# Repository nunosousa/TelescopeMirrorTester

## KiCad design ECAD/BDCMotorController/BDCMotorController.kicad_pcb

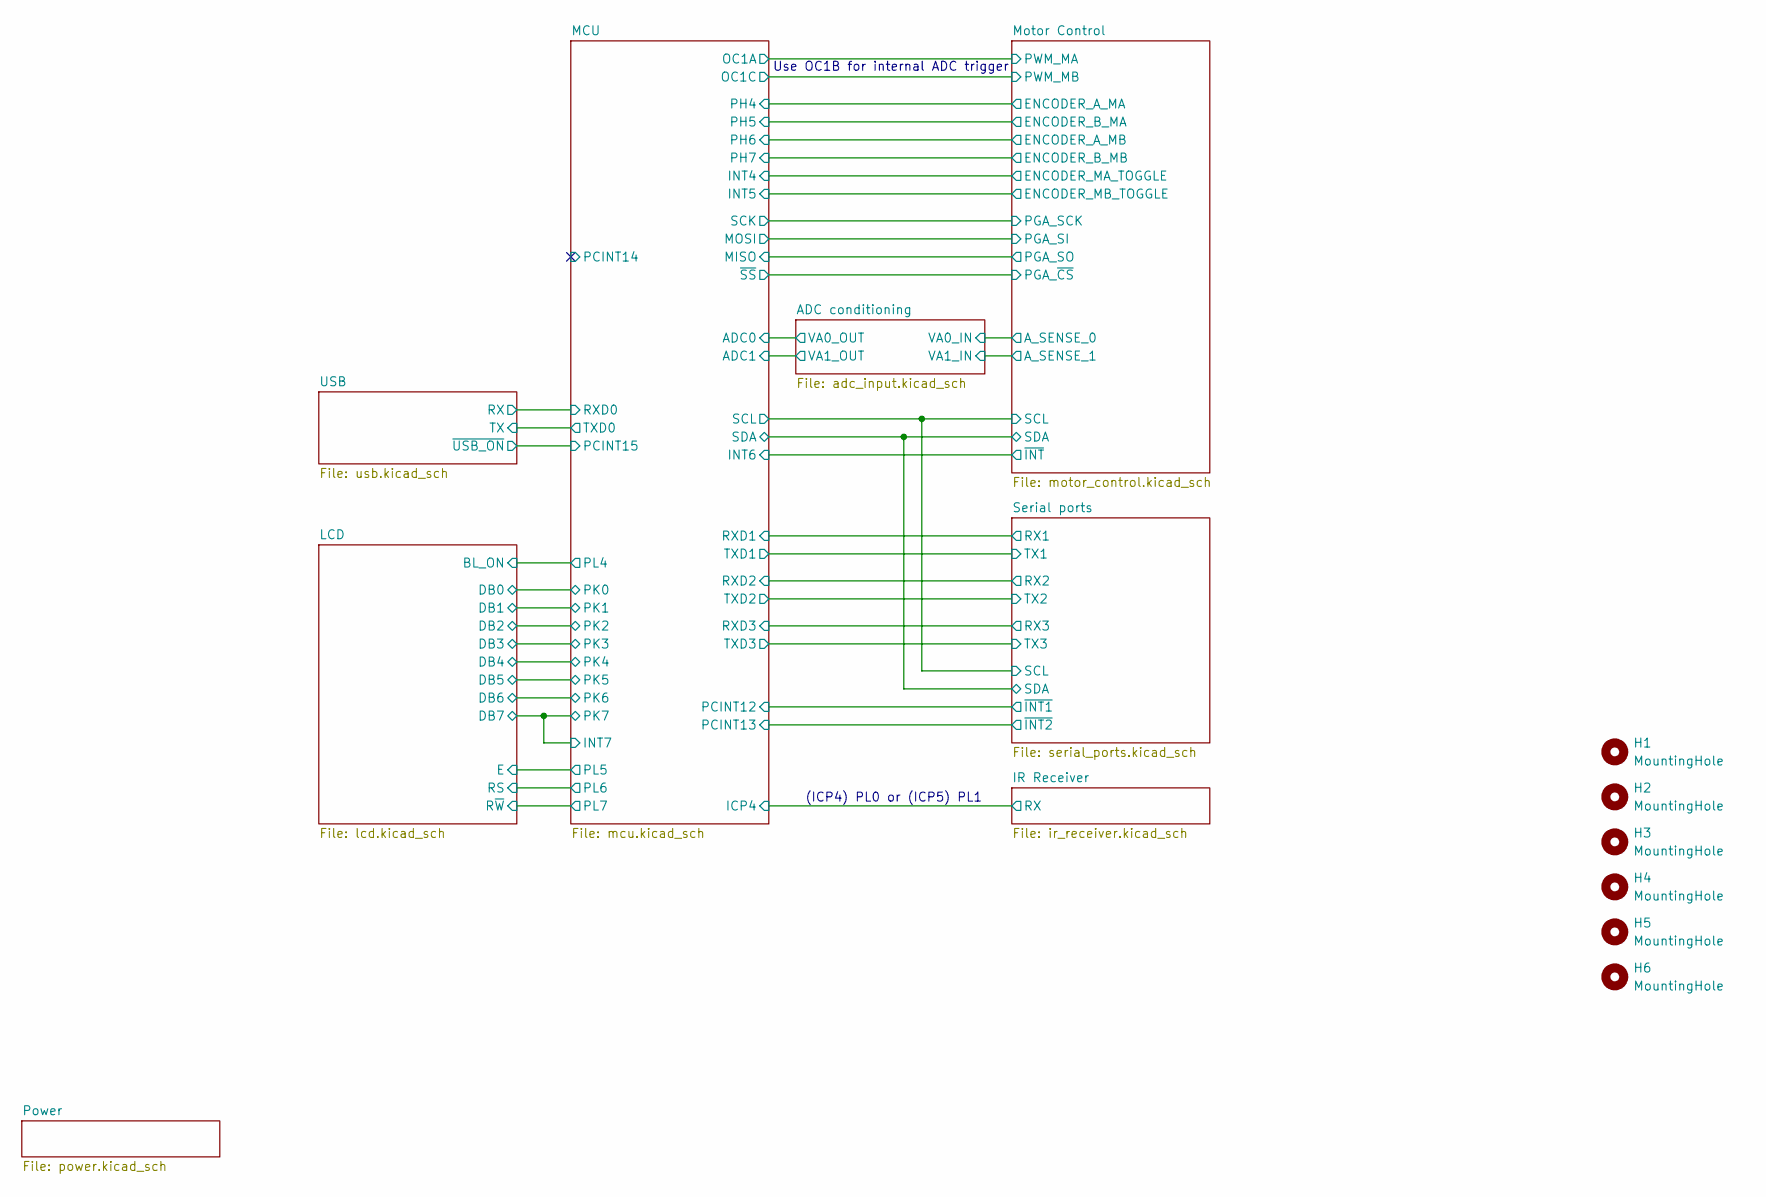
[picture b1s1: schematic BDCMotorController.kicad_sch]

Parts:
H1, H2, H3, H4, H5, H6: MountingHole; MountingHole_3.2mm_M3

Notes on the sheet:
Use OC1B for internal ADC trigger
(ICP4) PL0 or (ICP5) PL1

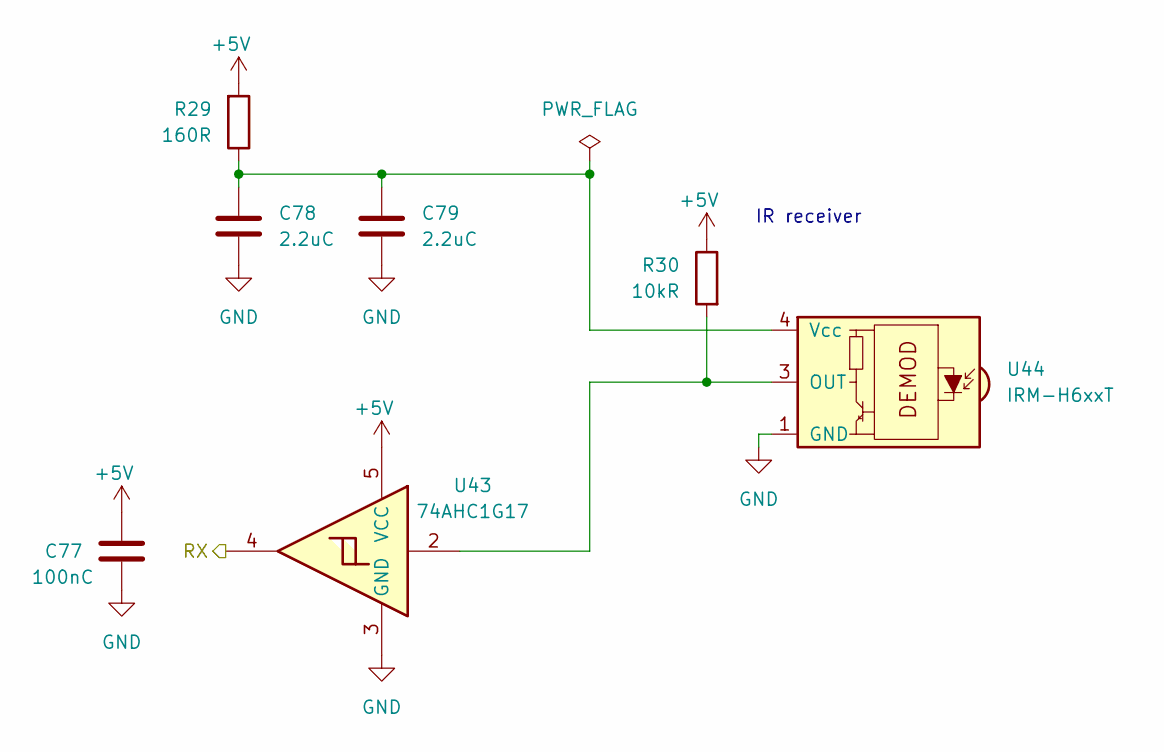
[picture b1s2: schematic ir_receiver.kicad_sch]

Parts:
C77: 100nC; C_0805_2012Metric
C78, C79: 2.2uC; C_0805_2012Metric
R29: 160R; R_0805_2012Metric; MPN AC0805FR-7W160RL
R30: 10kR; R_0805_2012Metric
U43: 74AHC1G17; SC-74A-5_1.55x2.9mm_P0.95mm; MPN 74AHC1G17GVH
U44: IRM-H6xxT; Everlight_IRM-H6xxT; MPN IRM-H638J7/TR2(CLW)

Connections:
+5V: C77.1, R29.2, R30.1, U43.5 (VCC); also elsewhere on the board
/IR Receiver/RX: U43.4; also elsewhere on the board
GND: C77.2, C78.2, C79.2, U43.3 (GND), U44.1 (GND), U44.2 (GND); also elsewhere on the board
unnamed: R30.2, U43.2, U44.3 (OUT)
unnamed: C78.1, C79.1, R29.1, U44.4 (Vcc)

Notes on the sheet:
IR receiver

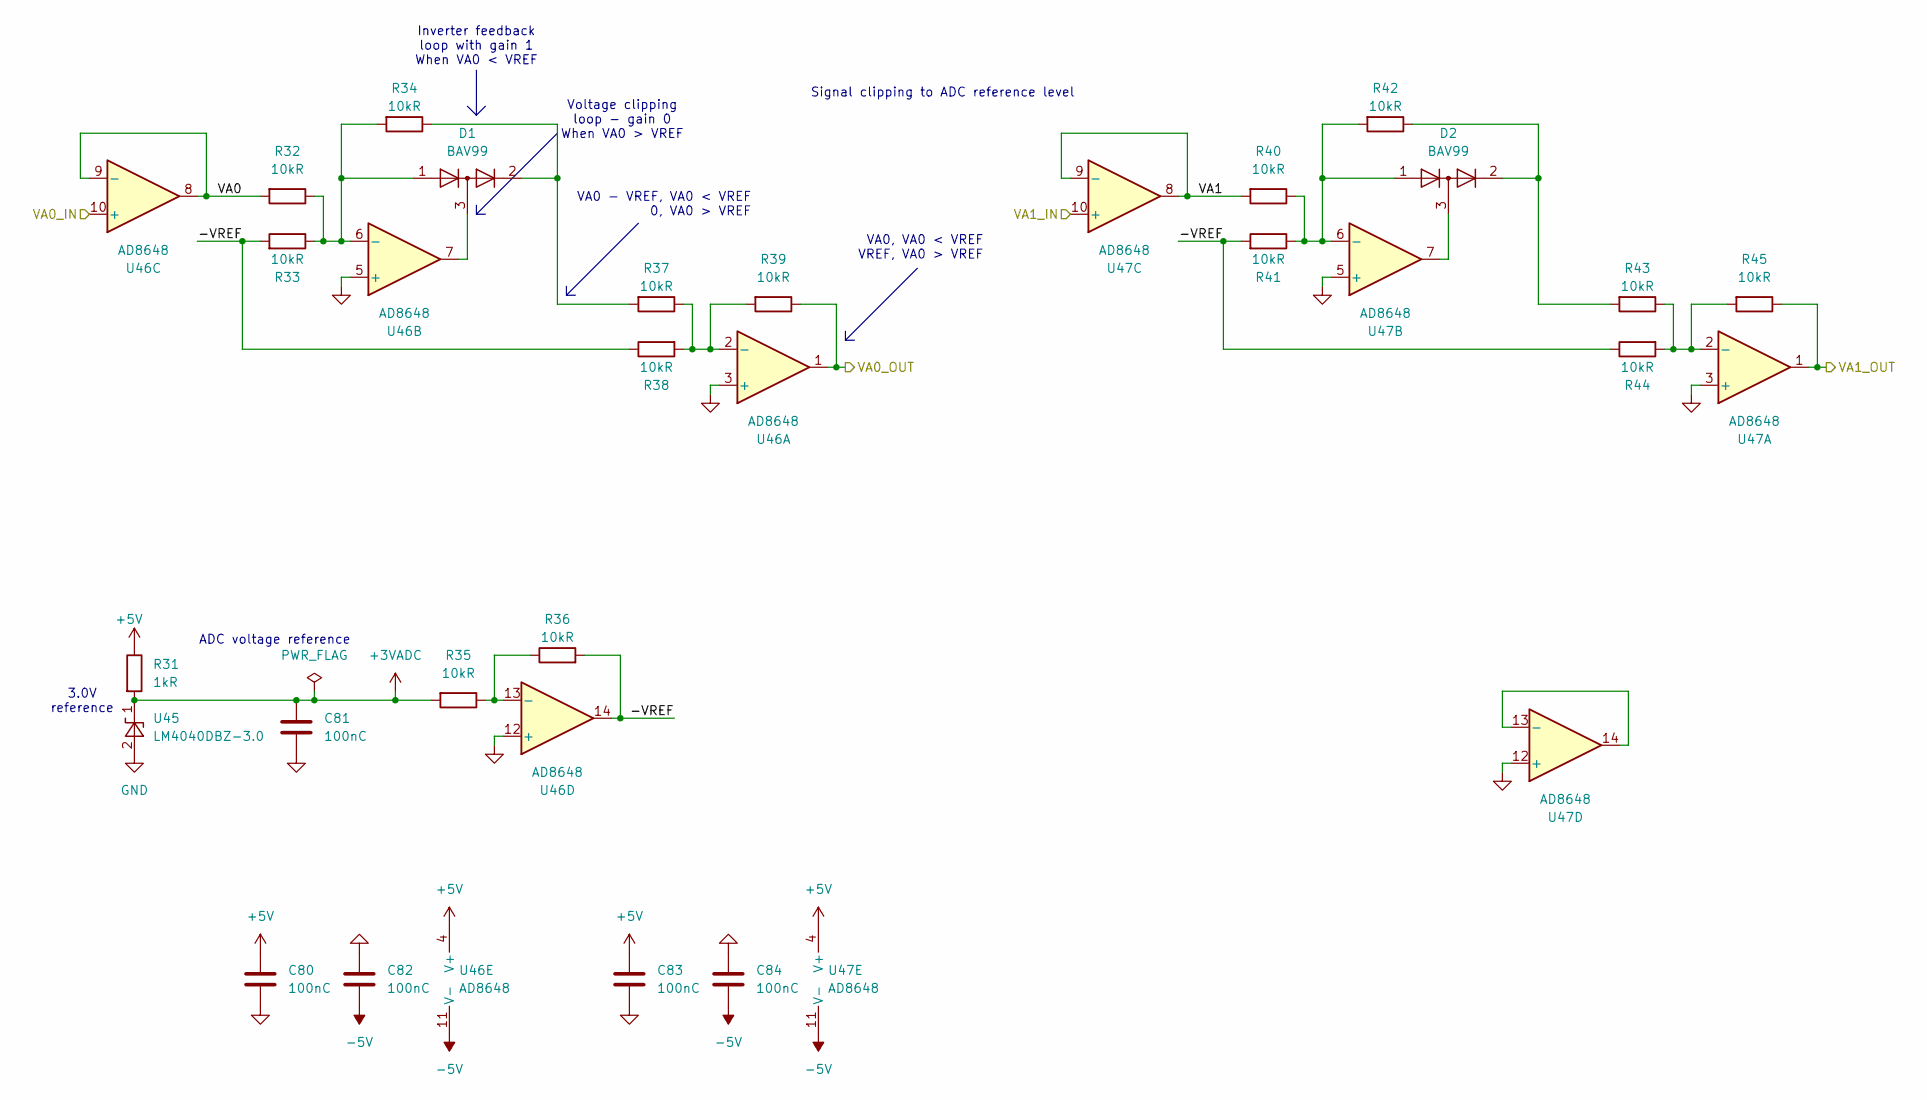
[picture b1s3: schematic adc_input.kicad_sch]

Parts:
C80, C81, C82, C83, C84: 100nC; C_0805_2012Metric
D1, D2: BAV99; SOT-23; MPN BAV99,215
R31: 1kR; R_0805_2012Metric
R32, R33, R34, R35, R36, R37, R38, R39, R40, R41, R42, R43, R44, R45: 10kR; R_0805_2012Metric
U45: LM4040DBZ-3.0; SOT-23; MPN LM4040B30IDBZR
U46, U47: AD8648; TSSOP-14_4.4x5mm_P0.65mm; MPN AD8648ARUZ

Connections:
+3VADC: C81.1, R31.2, R35.2, U45.1 (K); also elsewhere on the board
+5V: C80.1, C83.1, R31.1, U46.4 (V+), U47.4 (V+); also elsewhere on the board
-5V: C82.2, C84.2, U46.11 (V-), U47.11 (V-); also elsewhere on the board
/ADC conditioning/-VREF: R33.2, R36.2, R38.1, R41.2, R44.1, U46.14
/ADC conditioning/VA0: R32.2, U46.8, U46.9 (-)
/ADC conditioning/VA0_IN: U46.10 (+); also elsewhere on the board
/ADC conditioning/VA0_OUT: R39.1, U46.1; also elsewhere on the board
/ADC conditioning/VA1: R40.2, U47.8, U47.9 (-)
/ADC conditioning/VA1_IN: U47.10 (+); also elsewhere on the board
/ADC conditioning/VA1_OUT: R45.1, U47.1; also elsewhere on the board
GND: C80.2, C81.2, C82.1, C83.2, C84.1, U45.2 (A), U46.3 (+), U46.5 (+), U46.12 (+), U47.3 (+), U47.5 (+), U47.12 (+); also elsewhere on the board
unnamed: D1.2 (A), R34.1, R37.2
unnamed: D1.3 (K), U46.7
unnamed: D2.2 (A), R42.1, R43.2
unnamed: D2.3 (K), U47.7
unnamed: R37.1, R38.2, R39.2, U46.2 (-)
unnamed: D1.1 (K), R32.1, R33.1, R34.2, U46.6 (-)
unnamed: R35.1, R36.1, U46.13 (-)
unnamed: R43.1, R44.2, R45.2, U47.2 (-)
unnamed: D2.1 (K), R40.1, R41.1, R42.2, U47.6 (-)
unnamed: U47.13 (-), U47.14

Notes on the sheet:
Inverter feedback loop with gain 1 When VA0 < VREF
3.0V reference
ADC voltage reference
Signal clipping to ADC reference level
Voltage clipping loop - gain 0 When VA0 > VREF
VA0, VA0 < VREF VREF, VA0 > VREF
VA0 - VREF, VA0 < VREF 0, VA0 > VREF

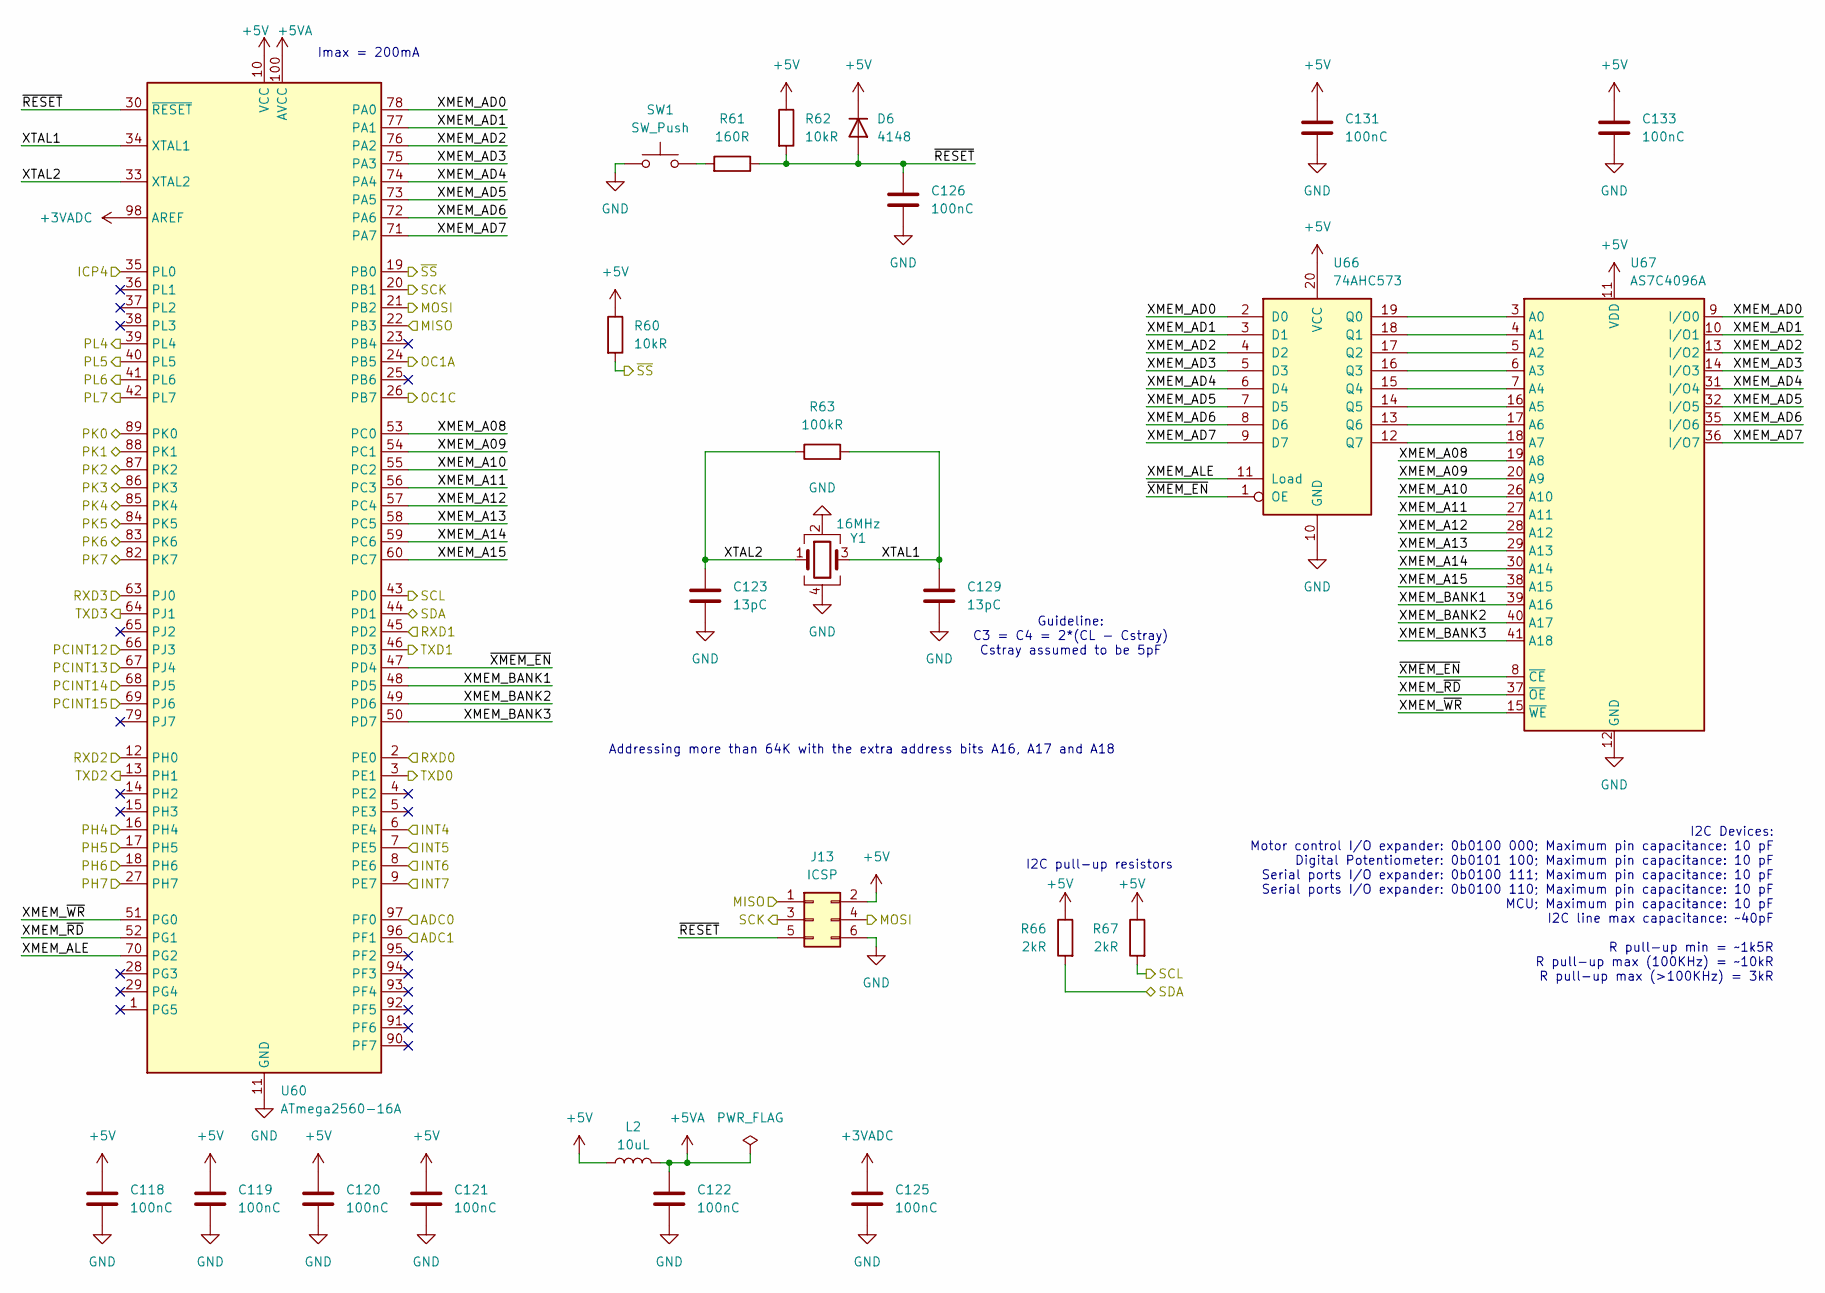
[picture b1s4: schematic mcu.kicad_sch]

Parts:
C118, C119, C120, C121, C122, C125, C126, C131, C133: 100nC; C_0805_2012Metric
C123, C129: 13pC; C_0805_2012Metric; MPN 0805CG130J500NT
D6: 4148; D_SOD-123; MPN MMSD4148T1G
J13: ICSP; PinHeader_2x03_P2.54mm_Vertical; MPN PZ254-2-03-Z-8.5
L2: 10uL; L_1210_3225Metric; MPN NLV32T-100J-EF
R60, R62: 10kR; R_0805_2012Metric
R61: 160R; R_0805_2012Metric; MPN AC0805FR-7W160RL
R63: 100kR; R_0805_2012Metric; MPN RT0805BRD07100KL
R66, R67: 2kR; R_0805_2012Metric
SW1: SW_Push; SW_PUSH_6mm_H13mm
U60: ATmega2560-16A; TQFP-100_14x14mm_P0.5mm; MPN ATMEGA2560-16AU
U66: 74AHC573; TSSOP-20_4.4x6.5mm_P0.65mm; MPN 74AHC573PW,118
U67: AS7C4096A; TSOP-II-44_10.16x18.41mm_P0.8mm; MPN AS7C4096A-12TIN
Y1: 16MHz; Crystal_SMD_3225-4Pin_3.2x2.5mm; MPN X1E0000210119

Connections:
+3VADC: C125.1, U60.98 (AREF); also elsewhere on the board
+5V: C118.1, C119.1, C120.1, C121.1, C131.1, C133.1, D6.1 (K), J13.2, L2.1, R60.1, R62.1, R66.1, R67.1, U60.10 (VCC), U60.31 (VCC), U60.61 (VCC), U60.80 (VCC), U66.20 (VCC), U67.11 (VDD), U67.33 (VDD); also elsewhere on the board
+5VA: C122.1, L2.2, U60.100 (AVCC)
/ADC conditioning/VA0_OUT: U60.97 (PF0); also elsewhere on the board
/ADC conditioning/VA1_OUT: U60.96 (PF1); also elsewhere on the board
/IR Receiver/RX: U60.35 (PL0); also elsewhere on the board
/LCD/BL_ON: U60.39 (PL4); also elsewhere on the board
/LCD/DB0: U60.89 (PK0); also elsewhere on the board
/LCD/DB1: U60.88 (PK1); also elsewhere on the board
/LCD/DB2: U60.87 (PK2); also elsewhere on the board
/LCD/DB3: U60.86 (PK3); also elsewhere on the board
/LCD/DB4: U60.85 (PK4); also elsewhere on the board
/LCD/DB5: U60.84 (PK5); also elsewhere on the board
/LCD/DB6: U60.83 (PK6); also elsewhere on the board
/LCD/DB7: U60.9 (PE7), U60.82 (PK7); also elsewhere on the board
/LCD/E: U60.40 (PL5); also elsewhere on the board
/LCD/RS: U60.41 (PL6); also elsewhere on the board
/LCD/R~W: U60.42 (PL7); also elsewhere on the board
/MCU/INT4: U60.6 (PE4); also elsewhere on the board
/MCU/INT5: U60.7 (PE5); also elsewhere on the board
/MCU/INT6: U60.8 (PE6); also elsewhere on the board
/MCU/MISO: J13.1, U60.22 (PB3); also elsewhere on the board
/MCU/MOSI: J13.4, U60.21 (PB2); also elsewhere on the board
/MCU/OC1A: U60.24 (PB5); also elsewhere on the board
/MCU/OC1C: U60.26 (PB7); also elsewhere on the board
/MCU/PCINT12: U60.66 (PJ3); also elsewhere on the board
/MCU/PCINT13: U60.67 (PJ4); also elsewhere on the board
/MCU/PCINT14: U60.68 (PJ5)
/MCU/PCINT15: U60.69 (PJ6); also elsewhere on the board
/MCU/PH4: U60.16 (PH4); also elsewhere on the board
/MCU/PH5: U60.17 (PH5); also elsewhere on the board
/MCU/PH6: U60.18 (PH6); also elsewhere on the board
/MCU/PH7: U60.27 (PH7); also elsewhere on the board
/MCU/RXD0: U60.2 (PE0); also elsewhere on the board
/MCU/RXD1: U60.45 (PD2); also elsewhere on the board
/MCU/RXD2: U60.12 (PH0); also elsewhere on the board
/MCU/RXD3: U60.63 (PJ0); also elsewhere on the board
/MCU/SCK: J13.3, U60.20 (PB1); also elsewhere on the board
/MCU/SCL: R67.2, U60.43 (PD0); also elsewhere on the board
/MCU/SDA: R66.2, U60.44 (PD1); also elsewhere on the board
/MCU/TXD0: U60.3 (PE1); also elsewhere on the board
/MCU/TXD1: U60.46 (PD3); also elsewhere on the board
/MCU/TXD2: U60.13 (PH1); also elsewhere on the board
/MCU/TXD3: U60.64 (PJ1); also elsewhere on the board
/MCU/XMEM_A08: U60.53 (PC0), U67.19 (A8)
/MCU/XMEM_A09: U60.54 (PC1), U67.20 (A9)
/MCU/XMEM_A10: U60.55 (PC2), U67.26 (A10)
/MCU/XMEM_A11: U60.56 (PC3), U67.27 (A11)
/MCU/XMEM_A12: U60.57 (PC4), U67.28 (A12)
/MCU/XMEM_A13: U60.58 (PC5), U67.29 (A13)
/MCU/XMEM_A14: U60.59 (PC6), U67.30 (A14)
/MCU/XMEM_A15: U60.60 (PC7), U67.38 (A15)
/MCU/XMEM_AD0: U60.78 (PA0), U66.2 (D0), U67.9 (I/O0)
/MCU/XMEM_AD1: U60.77 (PA1), U66.3 (D1), U67.10 (I/O1)
/MCU/XMEM_AD2: U60.76 (PA2), U66.4 (D2), U67.13 (I/O2)
/MCU/XMEM_AD3: U60.75 (PA3), U66.5 (D3), U67.14 (I/O3)
/MCU/XMEM_AD4: U60.74 (PA4), U66.6 (D4), U67.31 (I/O4)
/MCU/XMEM_AD5: U60.73 (PA5), U66.7 (D5), U67.32 (I/O5)
/MCU/XMEM_AD6: U60.72 (PA6), U66.8 (D6), U67.35 (I/O6)
/MCU/XMEM_AD7: U60.71 (PA7), U66.9 (D7), U67.36 (I/O7)
/MCU/XMEM_ALE: U60.70 (PG2), U66.11 (Load)
/MCU/XMEM_BANK1: U60.48 (PD5), U67.39 (A16)
/MCU/XMEM_BANK2: U60.49 (PD6), U67.40 (A17)
/MCU/XMEM_BANK3: U60.50 (PD7), U67.41 (A18)
/MCU/XMEM_~RD: U60.52 (PG1), U67.37 (~OE)
/MCU/XMEM_~WR: U60.51 (PG0), U67.15 (~WE)
/MCU/XTAL1: C129.1, R63.2, U60.34 (XTAL1), Y1.3
/MCU/XTAL2: C123.1, R63.1, U60.33 (XTAL2), Y1.1
/MCU/~RESET: C126.1, D6.2 (A), J13.5, R61.1, R62.2, U60.30 (~RESET)
/MCU/~SS: R60.2, U60.19 (PB0); also elsewhere on the board
/MCU/~XMEM_EN: U60.47 (PD4), U66.1 (OE), U67.8 (~CE)
GND: C118.2, C119.2, C120.2, C121.2, C122.2, C123.2, C125.2, C126.2, C129.2, C131.2, C133.2, J13.6, SW1.1, U60.11 (GND), U60.32 (GND), U60.62 (GND), U60.81 (GND), U60.99 (GND), U66.10 (GND), U67.12 (GND), U67.34 (GND), Y1.2, Y1.4; also elsewhere on the board
unnamed: R61.2, SW1.2
unnamed: U66.19 (Q0), U67.3 (A0)
unnamed: U66.18 (Q1), U67.4 (A1)
unnamed: U66.17 (Q2), U67.5 (A2)
unnamed: U66.16 (Q3), U67.6 (A3)
unnamed: U66.15 (Q4), U67.7 (A4)
unnamed: U66.14 (Q5), U67.16 (A5)
unnamed: U66.13 (Q6), U67.17 (A6)
unnamed: U66.12 (Q7), U67.18 (A7)

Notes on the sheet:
Imax = 200mA
Addressing more than 64K with the extra address bits A16, A17 and A18
I2C Devices: Motor control I/O expander: 0b0100 000; Maximum pin capacitance: 10 pF Digital Potentiometer: 0b0101 100; Maximum pin capacitance: 10 pF Serial ports I/O expander: 0b0100 111; Maximum pin capacitance: 10 pF Serial ports I/O expander: 0b0100 110; Maximum pin capacitance: 10 pF MCU; Maxi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
I2C pull-up resistors
Guideline: C3 = C4 = 2*(CL - Cstray) Cstray assumed to be 5pF

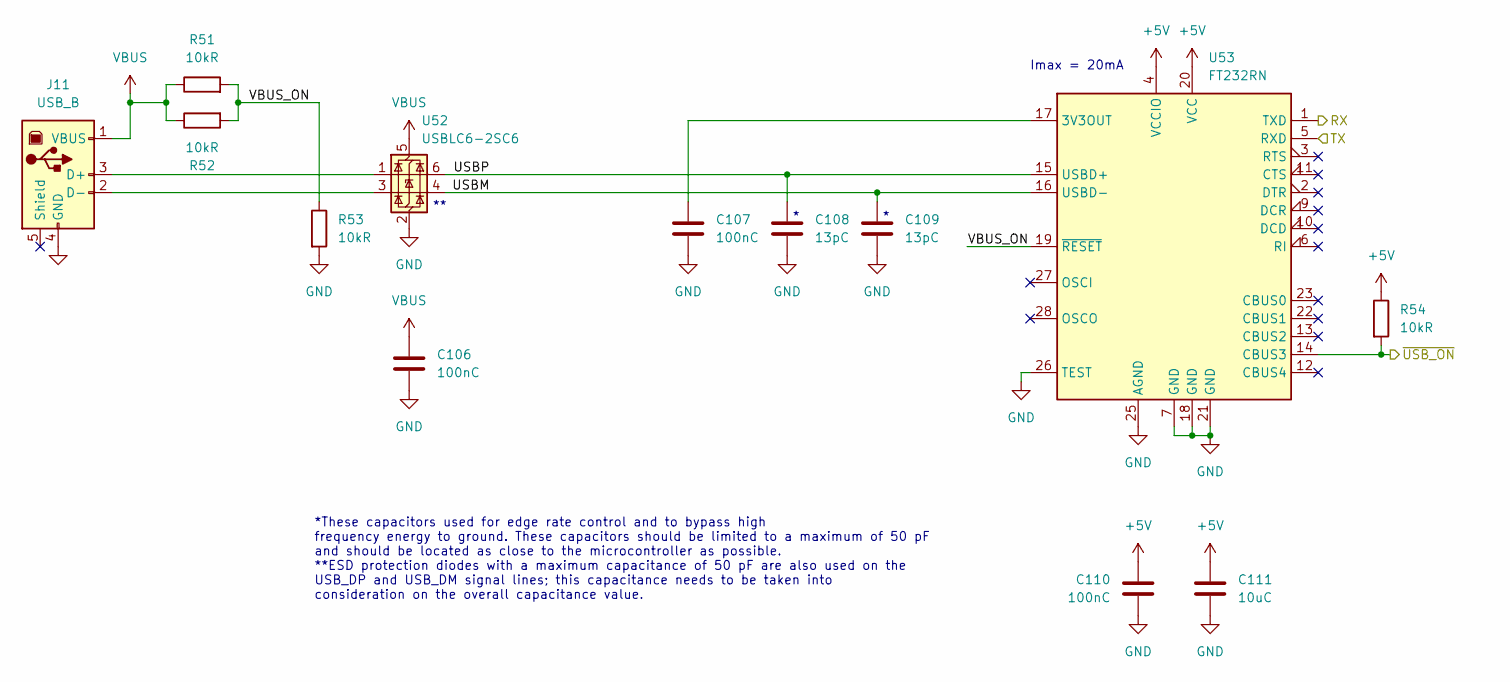
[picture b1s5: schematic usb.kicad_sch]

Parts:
C106, C107, C110: 100nC; C_0805_2012Metric
C108, C109: 13pC; C_0805_2012Metric; MPN 0805CG130J500NT
C111: 10uC; C_0805_2012Metric; MPN GRM21BR61E106MA73L
J11: USB_B; USB_B_TE_5787834_Vertical
R51, R52, R53, R54: 10kR; R_0805_2012Metric
U52: USBLC6-2SC6; SOT-23-6; MPN USBLC6-2SC6
U53: FT232RN; SSOP-28_5.3x10.2mm_P0.65mm; MPN FT232RNL-REEL

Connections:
+5V: C110.1, C111.1, R54.1, U53.4 (VCCIO), U53.20 (VCC); also elsewhere on the board
/MCU/PCINT15: R54.2, U53.14 (CBUS3); also elsewhere on the board
/MCU/RXD0: U53.1 (TXD); also elsewhere on the board
/MCU/TXD0: U53.5 (RXD); also elsewhere on the board
/USB/USBM: C109.1, U52.4 (I/O2), U53.16 (USBD-)
/USB/USBP: C108.1, U52.6 (I/O1), U53.15 (USBD+)
/USB/VBUS_ON: R51.2, R52.2, R53.1, U53.19 (~RESET)
GND: C106.2, C107.2, C108.2, C109.2, C110.2, C111.2, J11.4 (GND), R53.2, U52.2 (GND), U53.7 (GND), U53.18 (GND), U53.21 (GND), U53.25 (AGND), U53.26 (TEST); also elsewhere on the board
unnamed: J11.3 (D+), U52.1 (I/O1)
unnamed: J11.2 (D-), U52.3 (I/O2)
unnamed: C107.1, U53.17 (3V3OUT)
VBUS: C106.1, J11.1 (VBUS), R51.1, R52.1, U52.5 (VBUS)

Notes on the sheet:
Imax = 20mA
*These capacitors used for edge rate control and to bypass high frequency energy to ground. These capacitors should be limited to a maximum of 50 pF and should be located as close to the microcontroller as possible. **ESD protection diodes with a maximum capacitance of 50 pF are also used on the US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

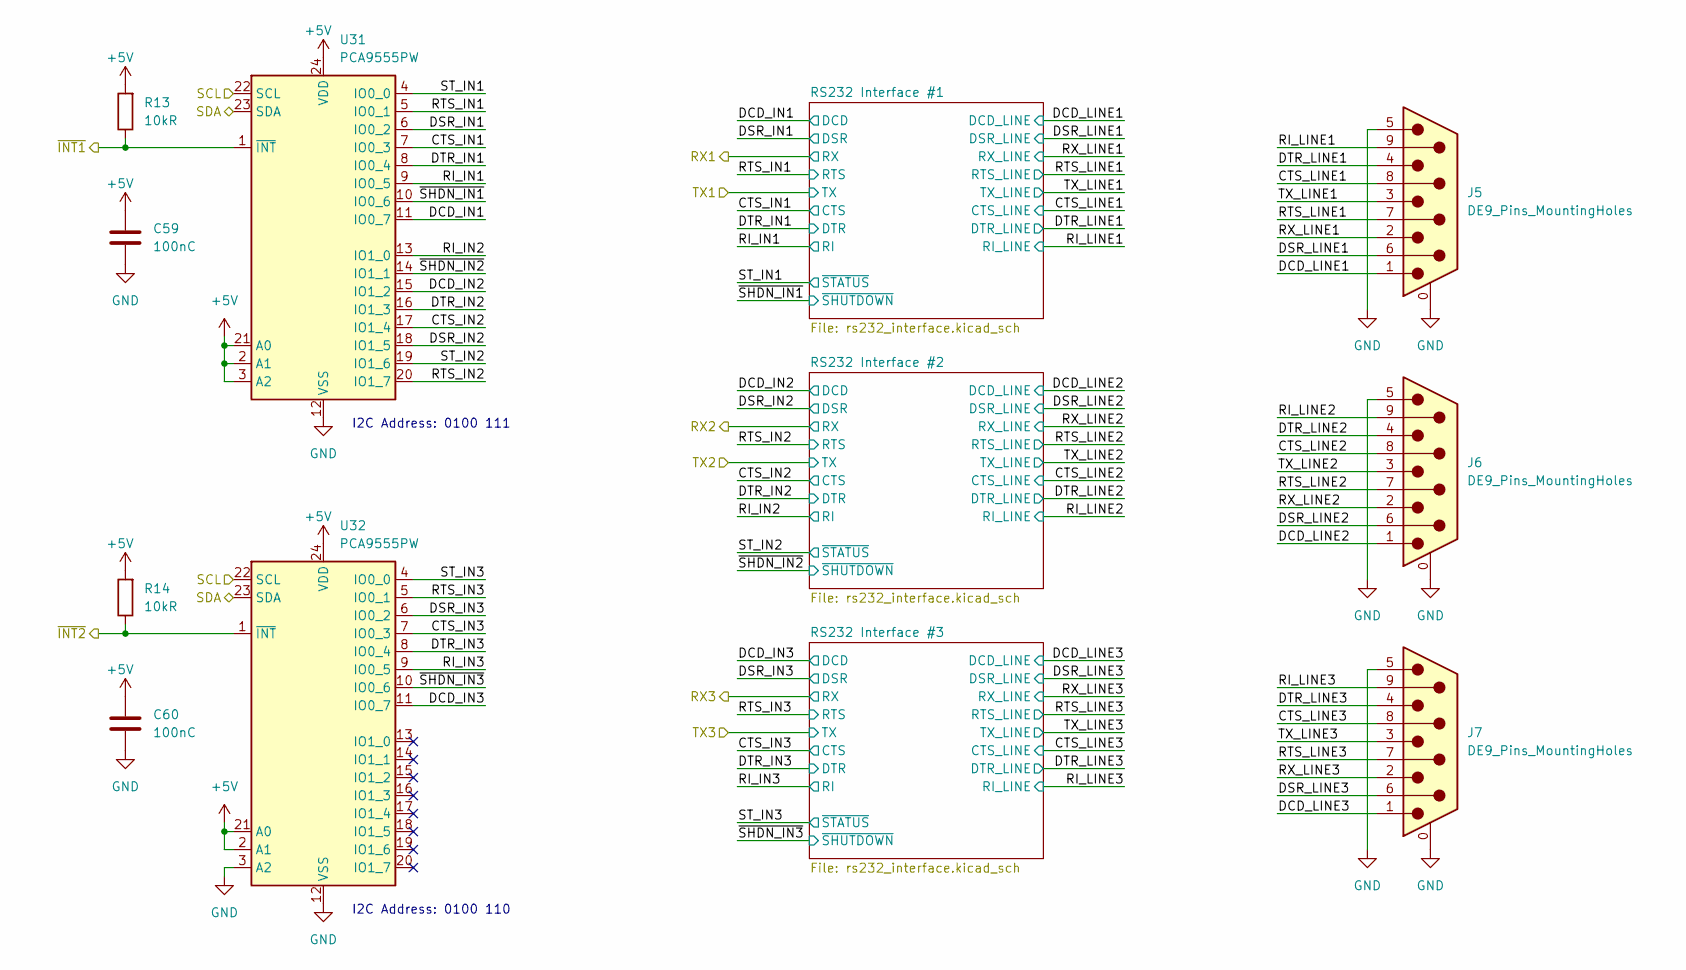
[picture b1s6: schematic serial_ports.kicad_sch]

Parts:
C59, C60: 100nC; C_0805_2012Metric
J5, J6, J7: DE9_Pins_MountingHoles; DSUB-9_Pins_Vertical_P2.77x2.84mm_MountingHoles
R13, R14: 10kR; R_0805_2012Metric
U31, U32: PCA9555PW; TSSOP-24_4.4x7.8mm_P0.65mm; MPN PCA9555PW,118

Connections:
+5V: C59.1, C60.1, R13.2, R14.2, U31.2 (A1), U31.3 (A2), U31.21 (A0), U31.24 (VDD), U32.2 (A1), U32.21 (A0), U32.24 (VDD); also elsewhere on the board
/MCU/PCINT12: R13.1, U31.1 (~INT); also elsewhere on the board
/MCU/PCINT13: R14.1, U32.1 (~INT); also elsewhere on the board
/MCU/SCL: U31.22 (SCL), U32.22 (SCL); also elsewhere on the board
/MCU/SDA: U31.23 (SDA), U32.23 (SDA); also elsewhere on the board
/Serial ports/CTS_IN1: U31.7 (IO0_3); also elsewhere on the board
/Serial ports/CTS_IN2: U31.17 (IO1_4); also elsewhere on the board
/Serial ports/CTS_IN3: U32.7 (IO0_3); also elsewhere on the board
/Serial ports/CTS_LINE1: J5.8; also elsewhere on the board
/Serial ports/CTS_LINE2: J6.8; also elsewhere on the board
/Serial ports/CTS_LINE3: J7.8; also elsewhere on the board
/Serial ports/DCD_IN1: U31.11 (IO0_7); also elsewhere on the board
/Serial ports/DCD_IN2: U31.15 (IO1_2); also elsewhere on the board
/Serial ports/DCD_IN3: U32.11 (IO0_7); also elsewhere on the board
/Serial ports/DCD_LINE1: J5.1; also elsewhere on the board
/Serial ports/DCD_LINE2: J6.1; also elsewhere on the board
/Serial ports/DCD_LINE3: J7.1; also elsewhere on the board
/Serial ports/DSR_IN1: U31.6 (IO0_2); also elsewhere on the board
/Serial ports/DSR_IN2: U31.18 (IO1_5); also elsewhere on the board
/Serial ports/DSR_IN3: U32.6 (IO0_2); also elsewhere on the board
/Serial ports/DSR_LINE1: J5.6; also elsewhere on the board
/Serial ports/DSR_LINE2: J6.6; also elsewhere on the board
/Serial ports/DSR_LINE3: J7.6; also elsewhere on the board
/Serial ports/DTR_IN1: U31.8 (IO0_4); also elsewhere on the board
/Serial ports/DTR_IN2: U31.16 (IO1_3); also elsewhere on the board
/Serial ports/DTR_IN3: U32.8 (IO0_4); also elsewhere on the board
/Serial ports/DTR_LINE1: J5.4; also elsewhere on the board
/Serial ports/DTR_LINE2: J6.4; also elsewhere on the board
/Serial ports/DTR_LINE3: J7.4; also elsewhere on the board
/Serial ports/RI_IN1: U31.9 (IO0_5); also elsewhere on the board
/Serial ports/RI_IN2: U31.13 (IO1_0); also elsewhere on the board
/Serial ports/RI_IN3: U32.9 (IO0_5); also elsewhere on the board
/Serial ports/RI_LINE1: J5.9; also elsewhere on the board
/Serial ports/RI_LINE2: J6.9; also elsewhere on the board
/Serial ports/RI_LINE3: J7.9; also elsewhere on the board
/Serial ports/RTS_IN1: U31.5 (IO0_1); also elsewhere on the board
/Serial ports/RTS_IN2: U31.20 (IO1_7); also elsewhere on the board
/Serial ports/RTS_IN3: U32.5 (IO0_1); also elsewhere on the board
/Serial ports/RTS_LINE1: J5.7; also elsewhere on the board
/Serial ports/RTS_LINE2: J6.7; also elsewhere on the board
/Serial ports/RTS_LINE3: J7.7; also elsewhere on the board
/Serial ports/RX_LINE1: J5.2; also elsewhere on the board
/Serial ports/RX_LINE2: J6.2; also elsewhere on the board
/Serial ports/RX_LINE3: J7.2; also elsewhere on the board
/Serial ports/ST_IN1: U31.4 (IO0_0); also elsewhere on the board
/Serial ports/ST_IN2: U31.19 (IO1_6); also elsewhere on the board
/Serial ports/ST_IN3: U32.4 (IO0_0); also elsewhere on the board
/Serial ports/TX_LINE1: J5.3; also elsewhere on the board
/Serial ports/TX_LINE2: J6.3; also elsewhere on the board
/Serial ports/TX_LINE3: J7.3; also elsewhere on the board
/Serial ports/~SHDN_IN1: U31.10 (IO0_6); also elsewhere on the board
/Serial ports/~SHDN_IN2: U31.14 (IO1_1); also elsewhere on the board
/Serial ports/~SHDN_IN3: U32.10 (IO0_6); also elsewhere on the board
GND: C59.2, C60.2, J5.0 (PAD), J5.5, J6.0 (PAD), J6.5, J7.0 (PAD), J7.5, U31.12 (VSS), U32.3 (A2), U32.12 (VSS); also elsewhere on the board

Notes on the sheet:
I2C Address: 0100 110
I2C Address: 0100 111

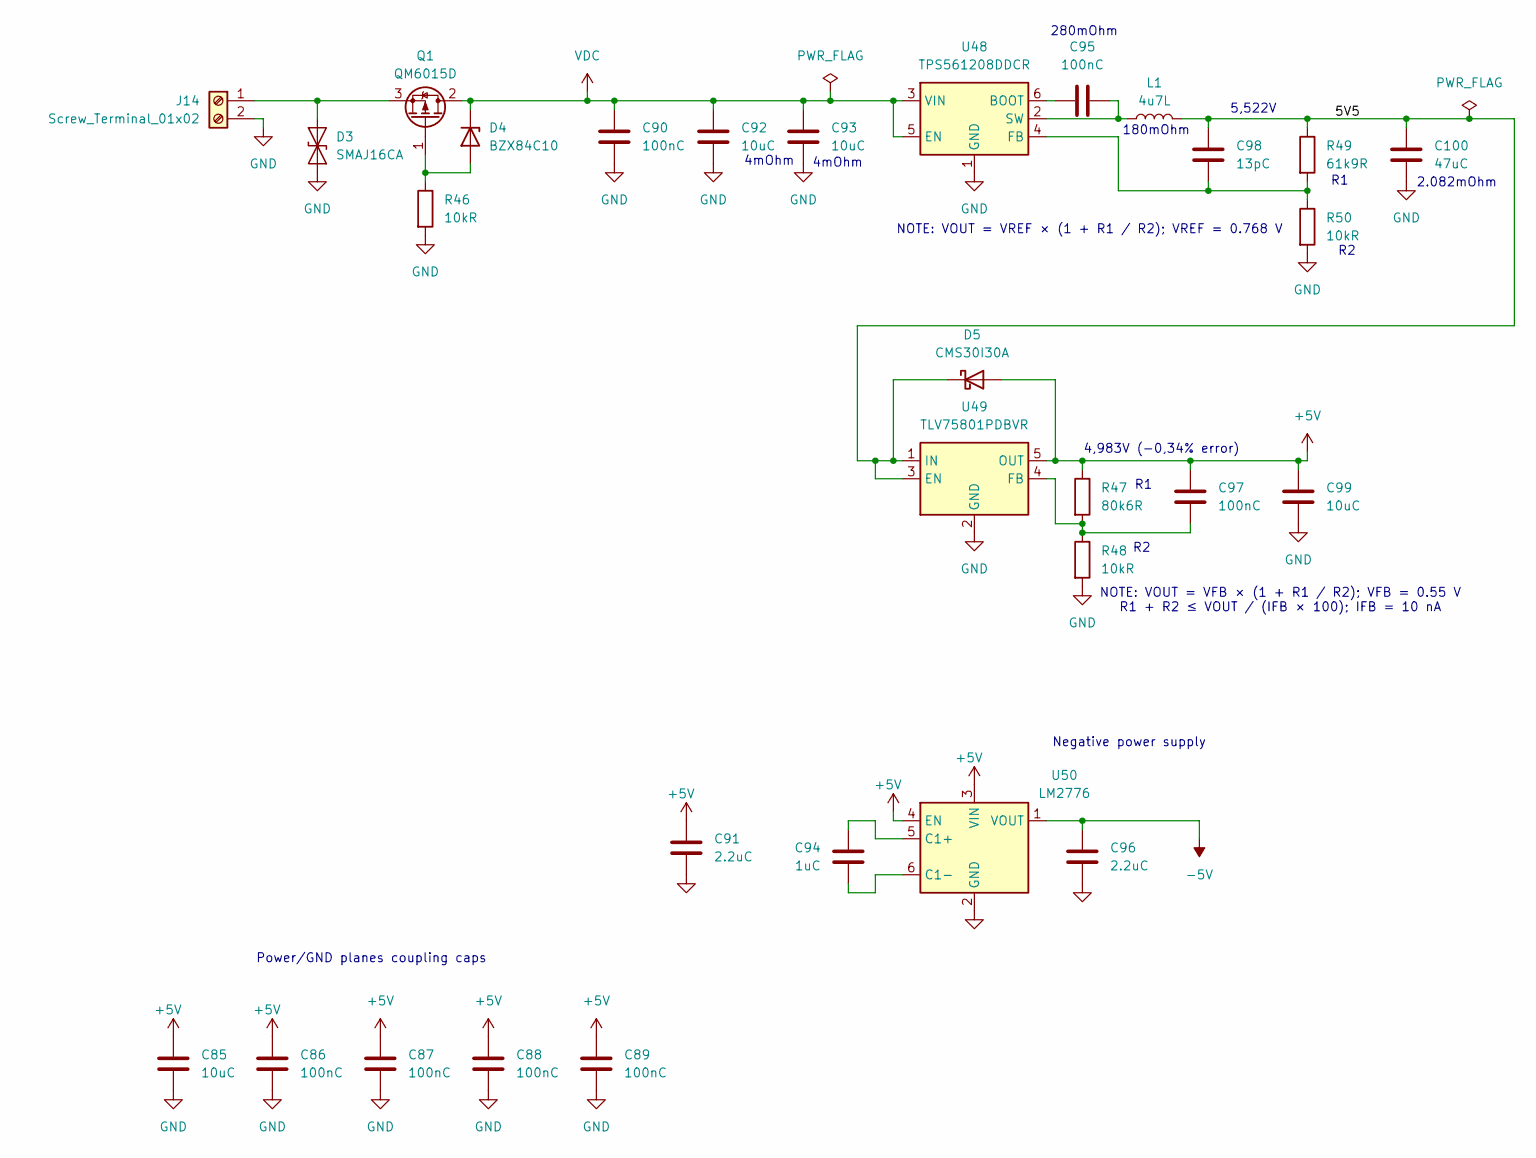
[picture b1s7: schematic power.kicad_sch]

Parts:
C85, C92, C93, C99: 10uC; C_0805_2012Metric; MPN GRM21BR61E106MA73L
C86, C87, C88, C89, C90, C95, C97: 100nC; C_0805_2012Metric
C91, C96: 2.2uC; C_0805_2012Metric
C94: 1uC; C_0805_2012Metric
C98: 13pC; C_0805_2012Metric; MPN 0805CG130J500NT
C100: 47uC; C_1210_3225Metric; MPN GRM32ER61C476KE15L
D3: SMAJ16CA; D_SMA
D4: BZX84C10; SOT-23; MPN BZX84C10-7-F
D5: CMS30I30A; D_SOD-128; MPN CMS30I30A(TE12L,QM
J14: Screw_Terminal_01x02; TerminalBlock_Phoenix_MPT-0,5-2-2.54_1x02_P2.54mm_Horizontal
L1: 4u7L; L_Vishay_IHLP-4040; MPN IHLP4040DZER4R7M01
Q1: QM6015D; TO-252-2
R46, R48, R50: 10kR; R_0805_2012Metric
R47: 80k6R; R_0805_2012Metric; MPN RT0805BRD0780K6L
R49: 61k9R; R_0805_2012Metric; MPN PTFR0805B61K9P9
U48: TPS561208DDCR; SOT-23-6; MPN TPS561208DDCR
U49: TLV75801PDBVR; SOT-23-5; MPN TLV75801PDBVR
U50: LM2776; SOT-23-6

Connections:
+5V: C85.1, C86.1, C87.2, C88.2, C89.2, C91.1, C97.1, C99.1, D5.2 (A), R47.1, U49.5 (OUT), U50.3 (VIN), U50.4 (EN); also elsewhere on the board
-5V: C96.1, U50.1 (VOUT); also elsewhere on the board
/Power/5V5: C98.1, C100.1, D5.1 (K), L1.2, R49.1, U49.1 (IN), U49.3 (EN)
GND: C85.2, C86.2, C87.1, C88.1, C89.1, C90.1, C91.2, C92.2, C93.2, C96.2, C99.2, C100.2, D3.1 (A1), J14.2, R46.2, R48.2, R50.2, U48.1 (GND), U49.2 (GND), U50.2 (GND); also elsewhere on the board
unnamed: D3.2 (A2), J14.1, Q1.3 (S)
unnamed: D4.1 (A), Q1.1 (G), R46.1
unnamed: C95.1, U48.6 (BOOT)
unnamed: C98.2, R49.2, R50.1, U48.4 (FB)
unnamed: C95.2, L1.1, U48.2 (SW)
unnamed: C97.2, R47.2, R48.1, U49.4 (FB)
unnamed: C94.1, U50.5 (C1+)
unnamed: C94.2, U50.6 (C1-)
VDC: C90.2, C92.1, C93.1, D4.3 (K), Q1.2 (D), U48.3 (VIN), U48.5 (EN); also elsewhere on the board

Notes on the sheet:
280mOhm
Power/GND planes coupling caps
180mOhm
4mOhm
Negative power supply
4,983V (-0,34% error)
2.082mOhm
NOTE: VOUT = VREF × (1 + R1 / R2); VREF = 0.768 V
NOTE: VOUT = VFB × (1 + R1 / R2); VFB = 0.55 V R1 + R2 ≤ VOUT / (IFB × 100); IFB = 10 nA
5,522V

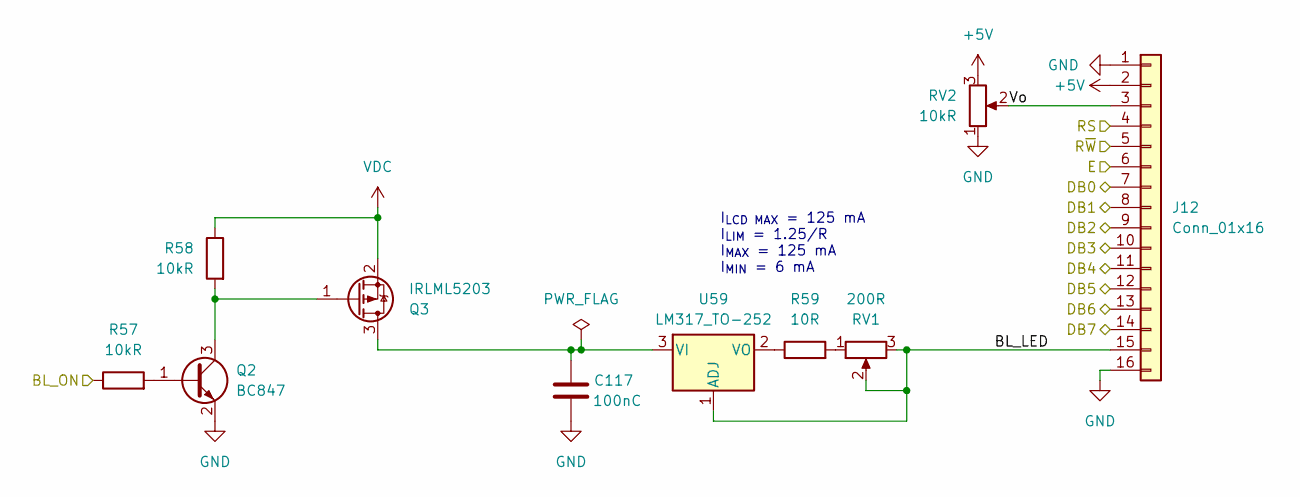
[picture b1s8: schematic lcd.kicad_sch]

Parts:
C117: 100nC; C_0805_2012Metric
J12: Conn_01x16; PinHeader_1x16_P2.54mm_Vertical
Q2: BC847; SOT-23; MPN BC847C,215
Q3: IRLML5203; SOT-23; MPN IRLML5203TRPBF
R57, R58: 10kR; R_0805_2012Metric
R59: 10R; R_0805_2012Metric
RV1: 200R; Potentiometer_Bourns_3296X_Horizontal; MPN 3296X-1-201LF
RV2: 10kR; Potentiometer_Bourns_3296X_Horizontal; MPN 3296X-1-103LF
U59: LM317_TO-252; TO-252-2; MPN LM317MDT-TR

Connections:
+5V: J12.2, RV2.3; also elsewhere on the board
/LCD/BL_LED: J12.15, RV1.2, RV1.3, U59.1 (ADJ)
/LCD/BL_ON: R57.1; also elsewhere on the board
/LCD/DB0: J12.7; also elsewhere on the board
/LCD/DB1: J12.8; also elsewhere on the board
/LCD/DB2: J12.9; also elsewhere on the board
/LCD/DB3: J12.10; also elsewhere on the board
/LCD/DB4: J12.11; also elsewhere on the board
/LCD/DB5: J12.12; also elsewhere on the board
/LCD/DB6: J12.13; also elsewhere on the board
/LCD/DB7: J12.14; also elsewhere on the board
/LCD/E: J12.6; also elsewhere on the board
/LCD/RS: J12.4; also elsewhere on the board
/LCD/R~W: J12.5; also elsewhere on the board
/LCD/Vo: J12.3, RV2.2
GND: C117.2, J12.1, J12.16, Q2.2 (E), RV2.1; also elsewhere on the board
unnamed: Q2.1 (B), R57.2
unnamed: Q2.3 (C), Q3.1 (G), R58.2
unnamed: C117.1, Q3.3 (D), U59.3 (VI)
unnamed: R59.2, RV1.1
unnamed: R59.1, U59.2 (VO)
VDC: Q3.2 (S), R58.1; also elsewhere on the board

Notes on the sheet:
I_{LCD MAX} = 125 mA I_{LIM} = 1.25/R I_{MAX} = 125 mA I_{MIN} = 6 mA
